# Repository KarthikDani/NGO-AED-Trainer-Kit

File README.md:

# NGO-AED-Trainer-Kit

- https://dronebotworkshop.com/esp32-i2s/
- https://github.com/schreibfaul1/ESP32-audioI2S

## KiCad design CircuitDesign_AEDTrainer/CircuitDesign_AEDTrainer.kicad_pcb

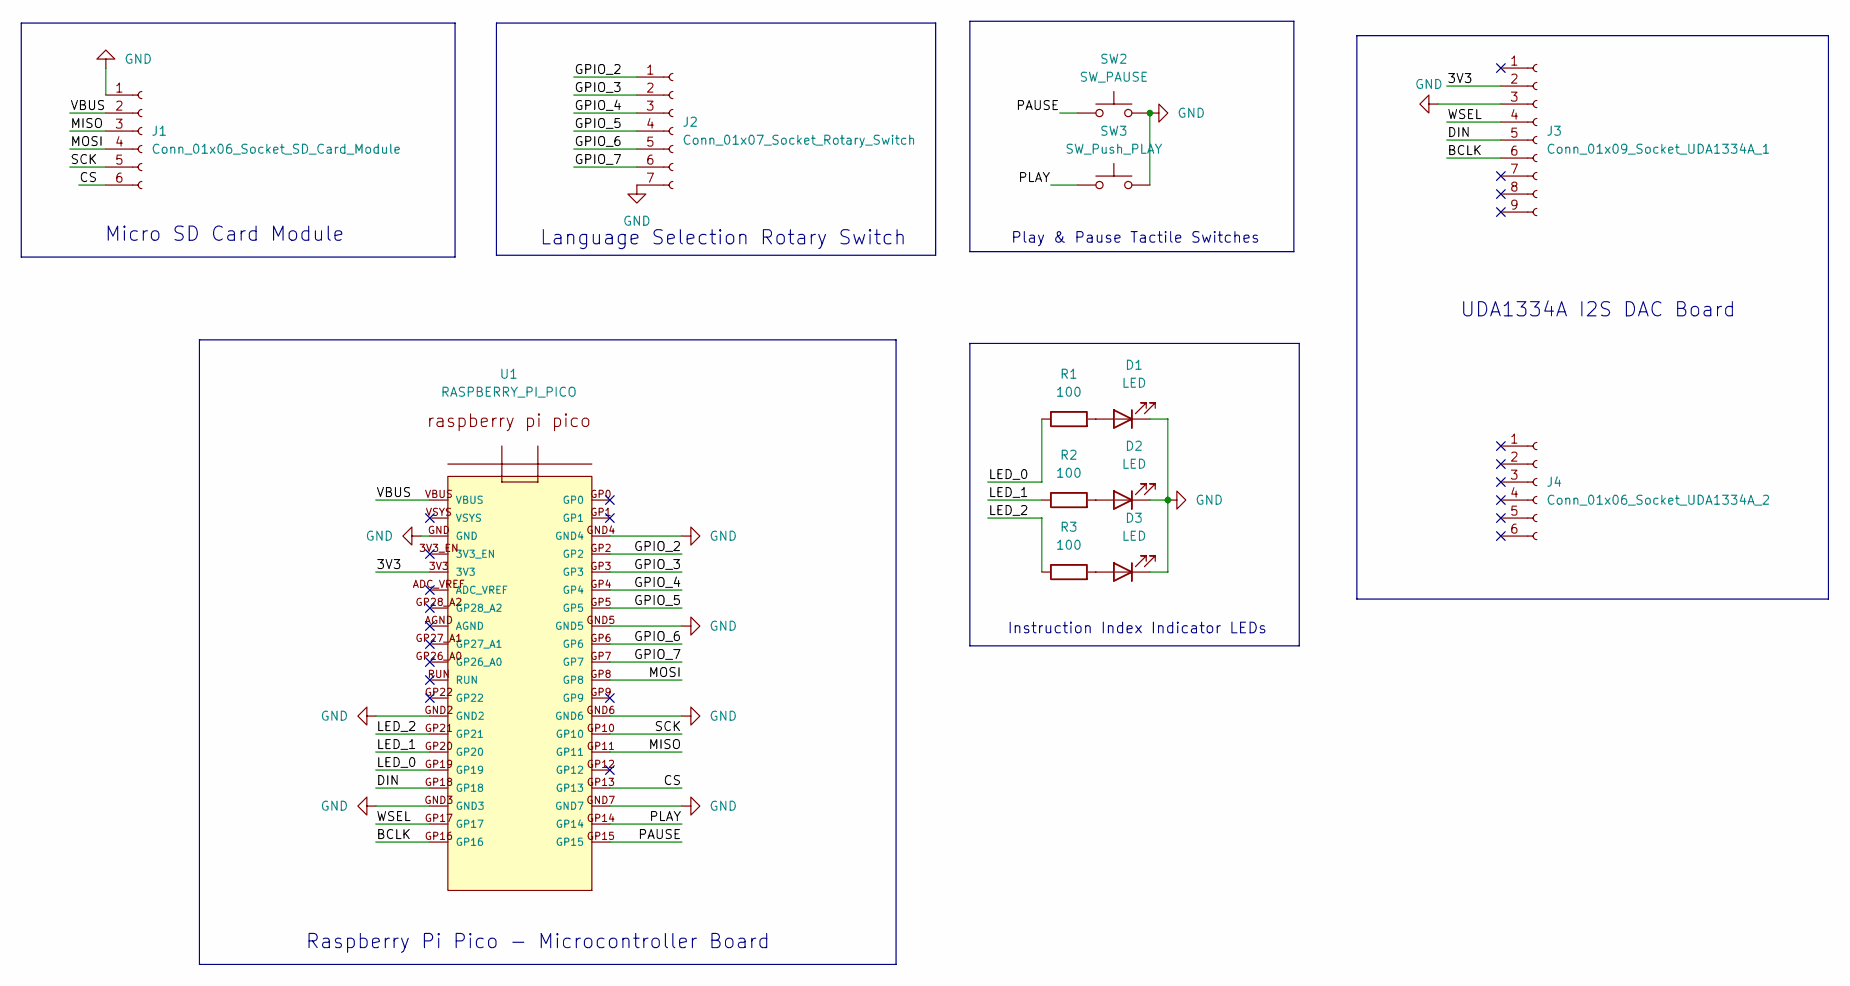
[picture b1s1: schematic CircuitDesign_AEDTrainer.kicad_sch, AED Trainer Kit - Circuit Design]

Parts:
D1, D2, D3: LED; LED_D3.0mm
J1: Conn_01x06_Socket_SD_Card_Module; PinSocket_1x06_P2.54mm_Horizontal
J2: Conn_01x07_Socket_Rotary_Switch; JST_XH_B7B-XH-A_1x07_P2.50mm_Vertical
J3: Conn_01x09_Socket_UDA1334A_1; PinSocket_1x09_P2.54mm_Vertical
J4: Conn_01x06_Socket_UDA1334A_2; PinSocket_1x06_P2.54mm_Vertical
R1, R2, R3: 100; R_Axial_DIN0309_L9.0mm_D3.2mm_P15.24mm_Horizontal
SW2: SW_PAUSE; SW_Tactile_Straight_KSL0Axx1LFTR
SW3: SW_Push_PLAY; SW_Tactile_Straight_KSL0Axx1LFTR
U1: RASPBERRY_PI_PICO

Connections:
/3V3: J3.2, U1.3V3
/BCLK: J3.6, U1.GP16
/CS: J1.6, U1.GP13
/DIN: J3.5, U1.GP18
/GPIO_2: J2.1, U1.GP2
/GPIO_3: J2.2, U1.GP3
/GPIO_4: J2.3, U1.GP4
/GPIO_5: J2.4, U1.GP5
/GPIO_6: J2.5, U1.GP6
/GPIO_7: J2.6, U1.GP7
/LED_0: R1.1, U1.GP19
/LED_1: R2.1, U1.GP20
/LED_2: R3.1, U1.GP21
/MISO: J1.3, U1.GP11
/MOSI: J1.4, U1.GP8
/PAUSE: SW2.1, U1.GP15
/PLAY: SW3.1, U1.GP14
/SCK: J1.5, U1.GP10
/VBUS: J1.2, U1.VBUS
/WSEL: J3.4, U1.GP17
GND: D1.1 (K), D2.1 (K), D3.1 (K), J1.1, J2.7, J3.3, SW2.2, SW3.2, U1.GND, U1.GND2, U1.GND3, U1.GND4, U1.GND5, U1.GND6, U1.GND7
unnamed: D1.2 (A), R1.2
unnamed: D2.2 (A), R2.2
unnamed: D3.2 (A), R3.2

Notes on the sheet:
Micro SD Card Module
Instruction Index Indicator LEDs
Raspberry Pi Pico - Microcontroller Board
Play & Pause Tactile Switches
UDA1334A I2S DAC Board
Language Selection Rotary Switch

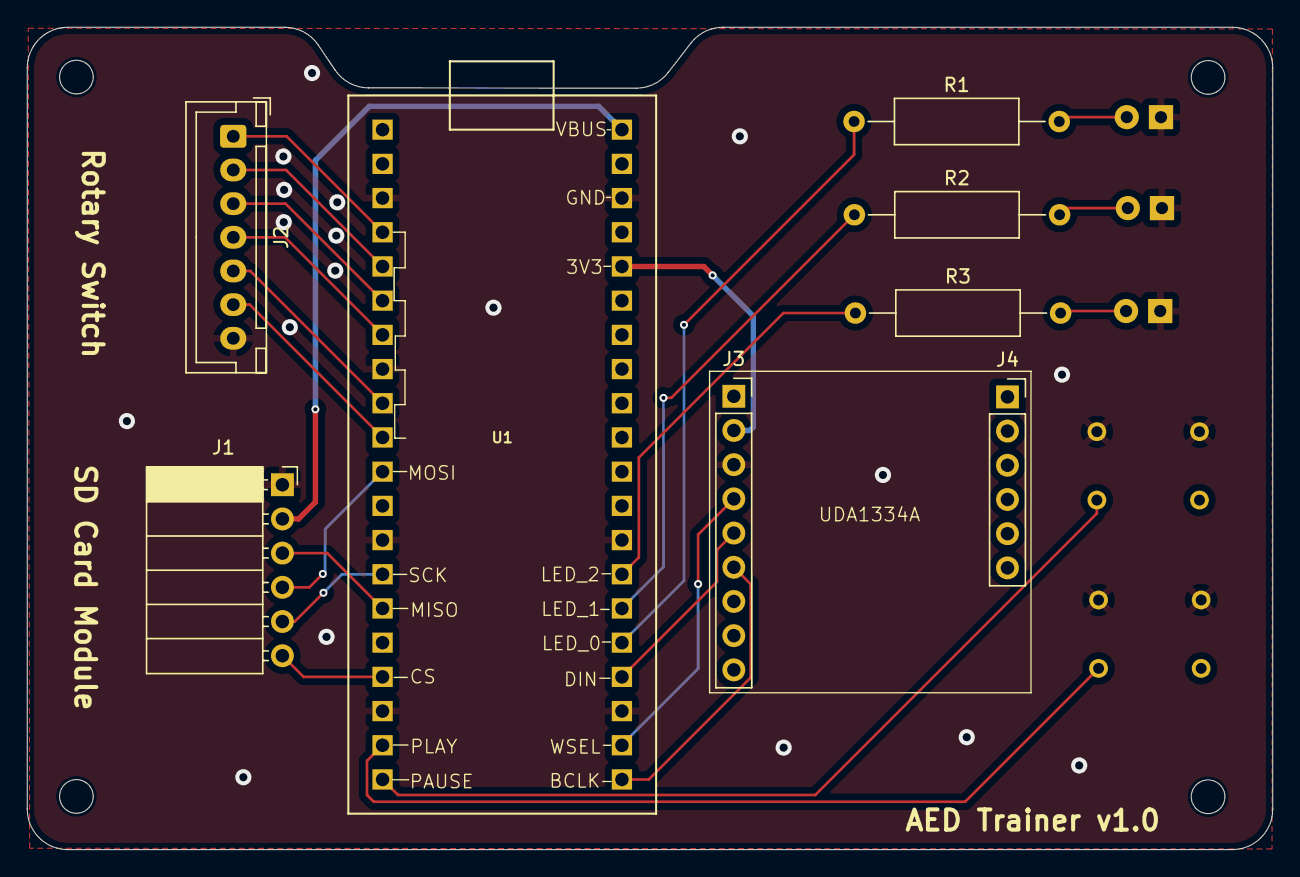
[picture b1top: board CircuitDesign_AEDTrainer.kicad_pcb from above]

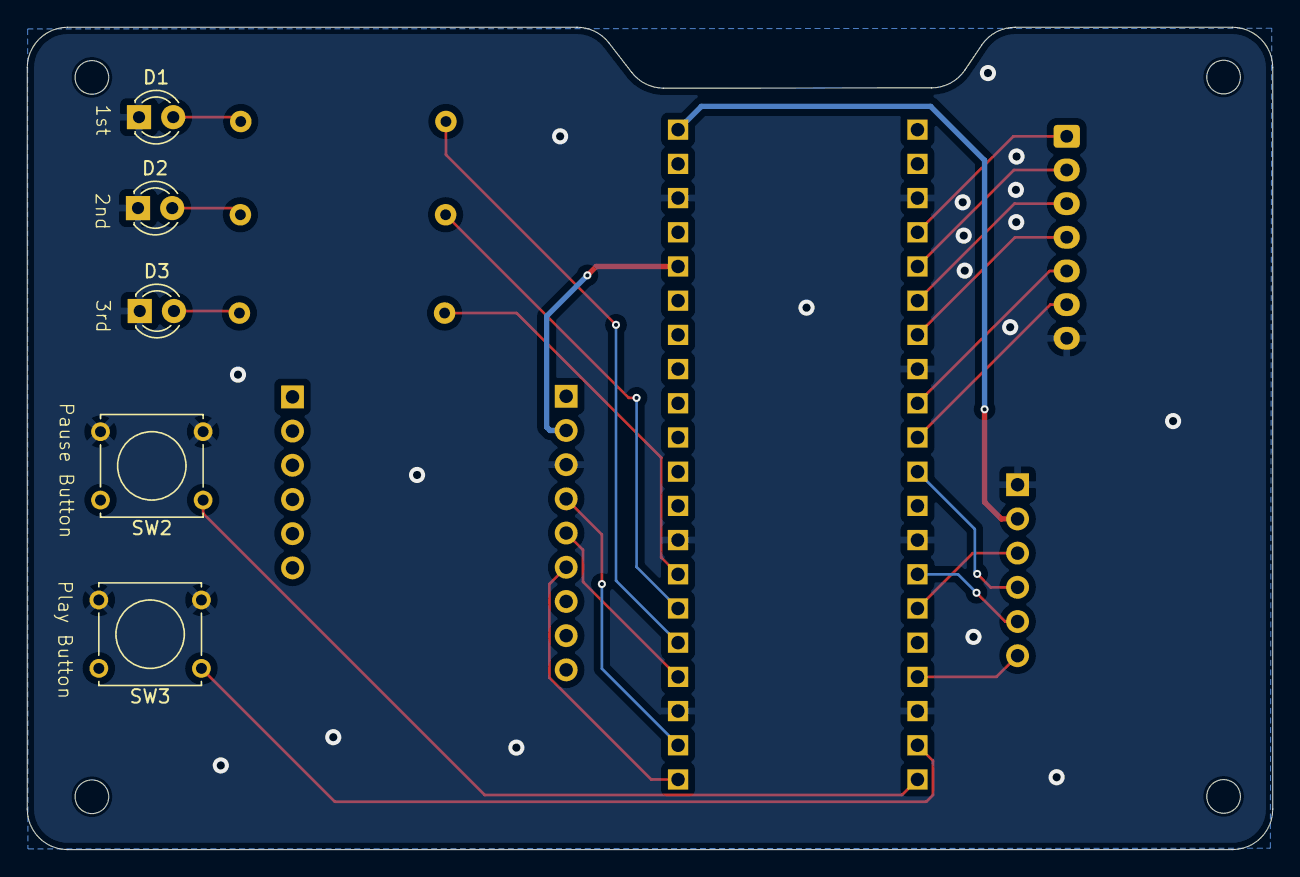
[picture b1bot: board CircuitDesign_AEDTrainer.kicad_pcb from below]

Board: 2 copper layers, 92.5 x 61.1 mm, 13 parts (5 on the bottom side), 24 nets.

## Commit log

2024-12-19 Repo created
2024-12-19 Some code added
2024-12-20 Implemented Audio play/stop, LED Indication + Debugs, Chronological start
2024-12-20 Circuit Diagram with KiCAD Done
2024-12-21 main code updated with some user friendly operation
2025-01-16 Audio files merged, Doubt NSS or SNN
2025-02-28 Completed. Audio Cracy because Amplitude to be adjusted
2025-03-01 44.1kHz + Structured Folder script ready. Card reader seems like gone
2025-03-01 All Audios clear! Sampling rate was problem; Prototype Completed!
2025-03-04 Schematics done, Footprints assigned
2025-03-05 Layout done
2025-04-09 Schematic change for SD Card
